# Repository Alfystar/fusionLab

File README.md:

# FusionLab
Fusion-Lab Prototype for the Tor Vergata University

Progetto a cura di Emanuele Alfano, sotto la supervisione del professore Daniele Carnevale

### Note attuali:

- [ElettricNote](02_Eletronics/ElettronicNote.md)
- [STM32Note](03_Code/STM32-miniTokamak/STM32Note.md)

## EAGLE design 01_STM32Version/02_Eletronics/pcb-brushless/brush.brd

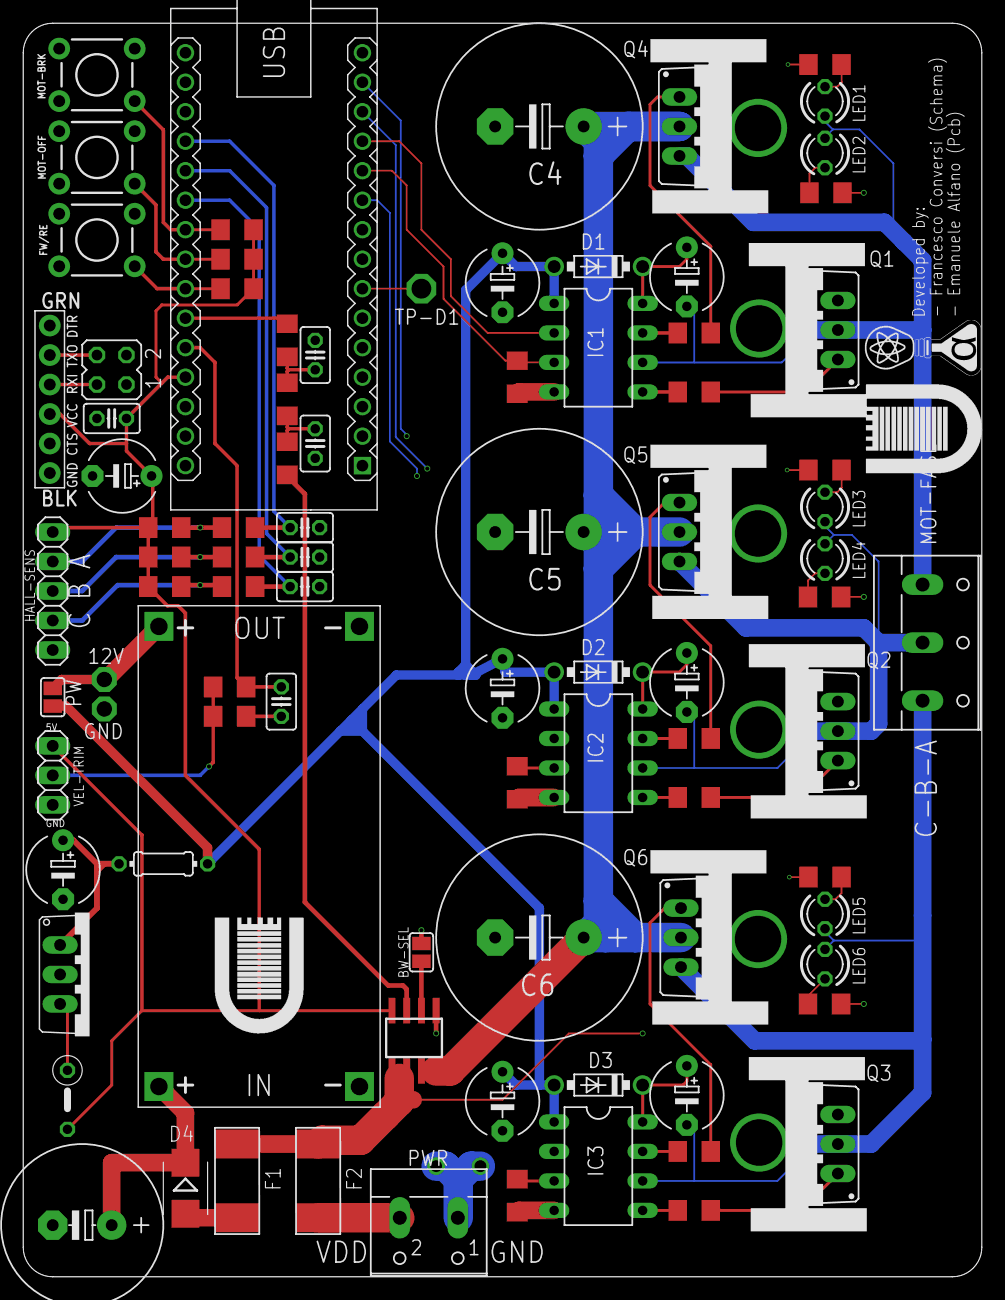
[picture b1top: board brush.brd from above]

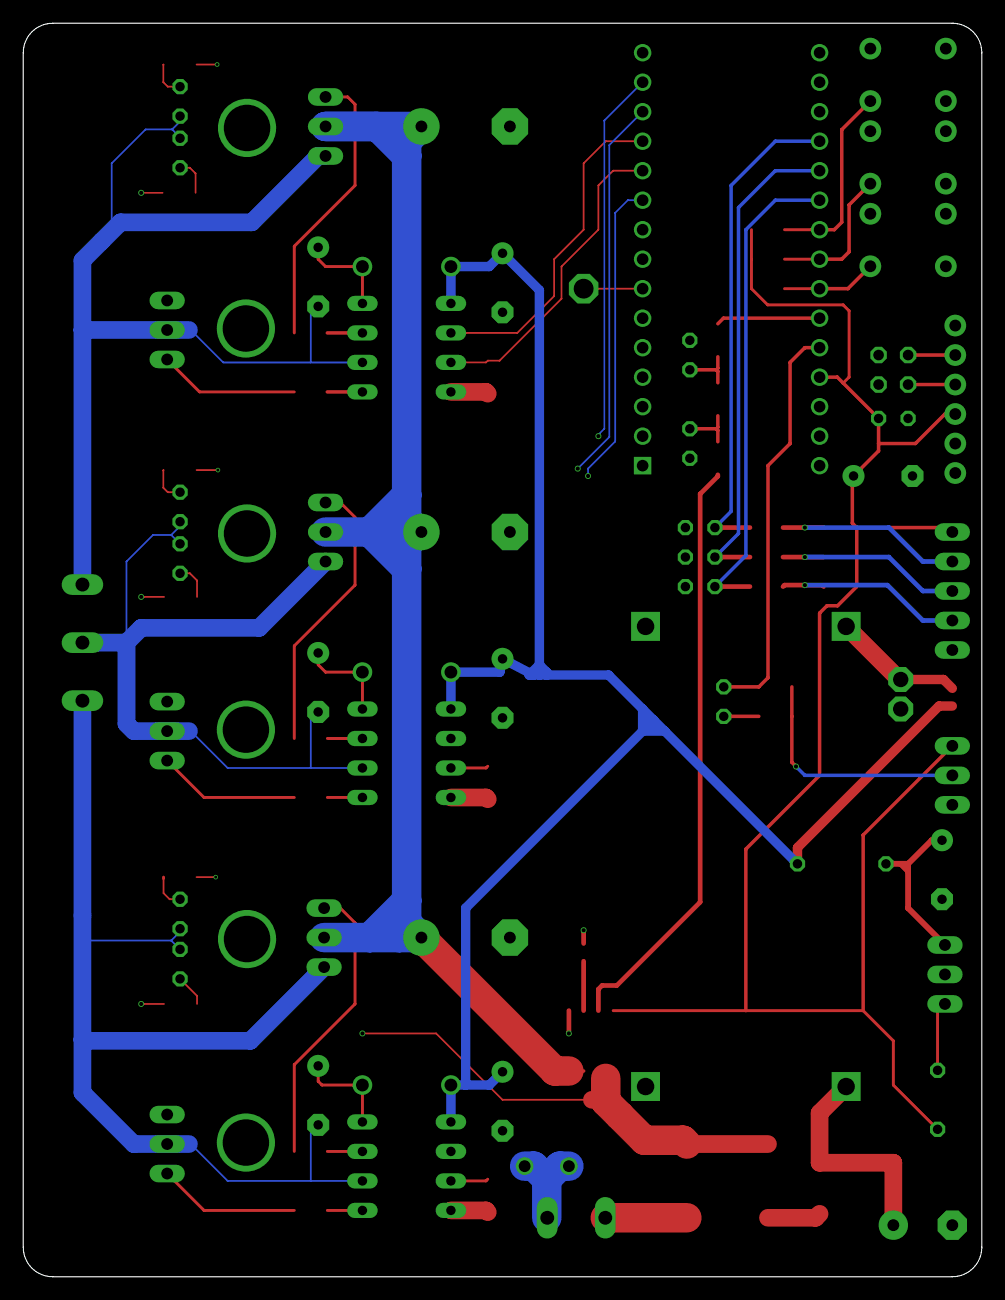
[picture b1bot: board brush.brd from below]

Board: 4 copper layers, 82.5 x 108.0 mm, 106 parts (7 on the bottom side), 72 nets.

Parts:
12V: TPSPAD1-13; P1-13
BW-SEL: SJ
C1, C2, C3: 2.2u; E5-6
C4, C5, C6: 270u/50V; E7,5-18
C7, C8, C9, C16, C19: 10u; E5-6
C10, C11, C12, C13, C15: 10n; C025-025X050
C14: 1n; C025-025X050
C17: 100n; C025-025X050
C18: 470u/50V; E5-13
D1, D2, D3: 1N5819-B; DO41-7.6
D4: ES2D; SMB
F1, F2: 2410-BOX; BELFUSE0679-3000-12
FW/RE: MOMENTARY-SWITCH-SPST-PTH-6.0MM; TACTILE_SWITCH_PTH_6.0MM
GND: TPSQPAD1-13; P1-13
HALL-SENS: 1X05
IC1, IC2, IC3: IR2108D; DIL08
IC4: ACS723; SOIC8
IC5: 7805TV; TO220V
J1: 6_PIN_SERIAL_TARGET_SIDE_W_SILK
JP1: JP2Q
L1: 10u; 0207/5V
LED1, LED2, LED3, LED4, LED5, LED6: LED3MM
M1: ARDUINO-NANO-3.0
MOT-BRK: MOMENTARY-SWITCH-SPST-PTH-6.0MM; TACTILE_SWITCH_PTH_6.0MM
MOT-FASE: W237-103
MOT-OFF: MOMENTARY-SWITCH-SPST-PTH-6.0MM; TACTILE_SWITCH_PTH_6.0MM
PW: SJ
PW$1: DC/DC-STEP-DOWNOLD-ALFY; DC-DC-STEP-DOWN-LM2596-ALFY
PWR: W237-102
Q1, Q2, Q3, Q4, Q5, Q6: IRFB4310; TO220BV
R1, R2, R3, R4, R5, R6: 22; R1206
R7, R8, R9: 10k; R1206
R10: 100; R1206
R11, R12, R13, R14, R15, R16, R19, R20, R21: 1k; R1206
R17: 47k; R1206
R18: 22; 0204/7
R100, R101, R102, R103, R104, R105, R106, R107, R108: 5.6k; R1206
TP-D1: PTR1PAD1-17; P1-17
U$1, U$2, U$6, U$11, U$12, U$13, U$14: NET12X12; NET-NET_12X12MIL
U$3, U$4, U$7, U$8, U$9, U$10: DISSTO-220; TO-220
U$15, U$16: TOR_10MM
U$17: ALFY_10MM
U$100: 3NET25X50MIL; 3NET-25X50MIL
VEL-TRIM: 1X03

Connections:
+5V: C16.+, C17.1, HALL-SENS.1, IC4.8, J1.P$4, L1.2, M1.J2.4, R19.2, R20.2, R21.2, R100.1, R101.1, R102.1, VEL-TRIM.1
+12V: C7.+, C8.+, C9.+, D1.A, D2.A, D3.A, IC1.1, IC2.1, IC3.1, PW.2, R18.2
A: MOT-FASE.1, Q1.D, Q4.S, U$1.N2, U$11.N2
A-SENS: LED1.A, LED2.K, U$1.N1
B: MOT-FASE.2, Q2.D, Q5.S, U$2.N2, U$13.N2
B-SENS: LED3.A, LED4.K, U$2.N1
C: MOT-FASE.3, Q3.D, Q6.S, U$6.N2, U$12.N2
C-SENS: LED5.A, LED6.K, U$6.N1
F-A: HALL-SENS.2, R13.2, R19.1
F-B: HALL-SENS.3, R14.2, R20.1
F-C: HALL-SENS.4, R15.2, R21.1
FW/RE: FW/RE.1, M1.J2.7, R102.2
GND: BW-SEL.1, C10.2, C11.2, C12.2, C13.2, C14.2, C15.2, C16.-, C17.2, C18.-, C19.-, FW/RE.3, GND.TP, HALL-SENS.5, IC4.5, IC5.2, J1.P$6, M1.J1.4, M1.J2.2, MOT-BRK.3, MOT-OFF.3, PW$1.IN-, PW$1.OUT-, R17.2, U$100.S2, VEL-TRIM.3
IN_A: IC1.3, M1.J1.11, R7.2
IN_B: IC2.3, M1.J1.10, R8.2
IN_C: IC3.3, M1.J1.15, R9.2
I_MOT: M1.J2.6, R10.2
MOT_BRK: M1.J2.9, MOT-BRK.1, R100.2
MOT_OFF: M1.J2.8, MOT-OFF.1, R101.2
unnamed: IC1.7, R1.2
unnamed: IC1.5, R2.2
unnamed: Q4.G, R1.1
unnamed: Q1.G, R2.1
unnamed: IC2.7, R3.2
unnamed: Q5.G, R3.1
unnamed: IC2.5, R4.2
unnamed: Q2.G, R4.1
unnamed: IC3.7, R5.2
unnamed: Q6.G, R5.1
unnamed: IC3.5, R6.2
unnamed: Q3.G, R6.1
unnamed: F2.2, PWR.2
unnamed: 12V.TP, PW.1, PW$1.OUT+
unnamed: D4.A, F1.1
unnamed: PWR.1, U$100.COM
unnamed: LED2.A, R108.2
unnamed: LED1.K, R107.2
unnamed: C13.1, M1.J2.5, R16.2
unnamed: LED4.A, R106.2
unnamed: LED3.K, R105.2
unnamed: M1.J1.7, TP-D1.TP
unnamed: LED6.A, R104.2
unnamed: LED5.K, R103.2
unnamed: C18.+, D4.C, PW$1.IN+
unnamed: C15.1, R10.1, R11.1
unnamed: IC4.7, R12.2
unnamed: C19.+, IC5.1, R18.1
unnamed: IC5.3, L1.1
unnamed: BW-SEL.2, IC4.6
unnamed: R16.1, R17.1, VEL-TRIM.2
unnamed: J1.P$2, JP1.4
unnamed: J1.P$3, JP1.2
unnamed: C14.1, R11.2, R12.1
PHASE_A: C10.1, M1.J2.12, R13.1
PHASE_B: C11.1, M1.J2.11, R14.1
PHASE_C: C12.1, M1.J2.10, R15.1
PWM_A: IC1.2, M1.J1.12
PWM_B: IC2.2, M1.J1.13
PWM_C: IC3.2, M1.J1.14
RESET: J1.P$1, M1.J1.3
RXD: JP1.1, M1.J1.2
TXD: JP1.3, M1.J1.1
V+: F1.2, F2.1, IC4.1, IC4.2, U$14.N2
VBA: C1.+, D1.C, IC1.8
VBB: C2.+, D2.C, IC2.8
VBC: C3.+, D3.C, IC3.8
VCCINT: R104.1, R106.1, R108.1, U$14.N1
VDD: C4.+, C5.+, C6.+, IC4.3, IC4.4, Q4.D, Q5.D, Q6.D
VS-A: C1.-, IC1.6, U$11.N1
VS-B: C2.-, IC2.6, U$13.N1
VS-C: C3.-, IC3.6, U$12.N1
VSS: C4.-, C5.-, C6.-, C7.-, C8.-, C9.-, IC1.4, IC2.4, IC3.4, Q1.S, Q2.S, Q3.S, R7.1, R8.1, R9.1, R103.1, R105.1, R107.1, U$100.S1

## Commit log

2021-06-18 start Commit
2021-06-18 eletronic note
2021-06-28 start pwm work
2021-07-09 PWM with interrupt do
2021-07-13 adc & pwm ok
2021-07-14 PWM, ADC, SampleTime make
2021-07-14 Linux-STM32 comunication & controll
2021-07-14 Note varie Update
2021-07-18 purge emp
2021-07-18 EMP correct Repository+
2021-07-19 Presentazione
2021-07-19 submodule update
2021-07-19 presentation update
2021-07-21 ADC read check, PWM to be Debugged
2021-07-22 another presentation
2021-07-29 last presentation
2021-07-29 report
2021-09-09 Arduino version Project, PatformIO setup
2021-09-09 start store data
2021-09-09 repository reorder
2021-09-09 repo submodule
2021-09-09 data store 1ms
2021-09-09 data store home
2021-09-09 Matlab post-elaboration for experiment
2021-09-10 rapid shot develop
2021-09-10 Triangle aquisition & RapidShot Acquisition
2021-09-10 remote stop experiment
2021-09-10 deadzone experiment success
2021-09-11 tesi latex
2021-09-11 Ringraziamenti tesi
2021-09-12 indice e inizio tesi
2021-09-13 IBT2 experiment relation start
2021-09-13 start driver current tesi
2021-09-13 enea english report
2021-09-14 start proportional work
2021-09-14 start double integrator work
2021-09-14 primo inseguimento
2021-09-15 enea relation update
2021-09-15 corretto doppio integratore
2021-09-16 WIP Tesi
2021-09-16 corretto bibtex
2021-09-16 tesi WIP
2021-09-17 First success experiment
2021-09-17 filter experiment
2021-09-20 architetture update image
2021-09-20 Tesi WIP, Trasformatore
2021-09-21 Tesi WIP, Cap1 prima stesura end
2021-09-22 work forked for experiment and Marte2 prepare work
2021-09-22 Immagini per tesi da esperimento prese
2021-09-23 report enea 2
2021-09-23 moc reorder
2021-09-23 test k variati per performance
2021-09-24 controlledFW and MocMarte first relase
2021-09-24 marte2 moc stable
2021-09-24 Controlled Firmware go
2021-09-24 marteMoc select reference logic
2021-09-29 estimation pre-work
2021-09-30 start estimation work
2021-10-01 extimation wip
2021-10-02 Tesi introduzione scritta
2021-10-02 Tesi riletta al capitolo 3
2021-10-02 tesi latex reindented
2021-10-05 tesi wip capitolo stima prima stesura
2021-10-05 simulation matlab work
2021-10-05 tesi wip, modello teorico scritto
2021-10-07 tesi wip cap controllo reale writing
2021-10-07 tesi WIP, cap5 esperimenti matlab plot working
2021-10-07 tesi wip cap 5 grafici
2021-10-08 TESI End, start debug
2021-10-08 Tesi clear workSpace
2021-10-08 immagini clean
2021-10-08 Tesi primo rewach
2021-10-10 tesi 3°debug in corso
2021-10-10 Tesi, intro e fine corretti con nico
2021-10-11 get last experiment
2021-10-11 tesi pre revisone carnevale
2021-10-11 start presentazione
2021-10-12 tesi con correzioni
2021-10-12 ultime correzioni tesi
2021-10-13 tesi 'sbiancata' per stampa
2021-10-13 correzioni in stamperia
2021-10-13 start revisone carnevale
2021-10-14 image update
2021-10-14 immagini presentazione reference aggiunte
2021-10-14 circuit current equivalent
2021-10-14 correzioni su presentazione finite
2021-10-14 presentazione splittata per pdf

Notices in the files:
parts and their libraries:
diy-modules: Released under the Creative Commons Attribution 4.0 International License: http://creativecommons.org/licenses/by/4.0
SparkFun-Connectors: Licensing: Creative Commons ShareAlike 4.0 International - https://creativecommons.org/licenses/by-sa/4.0
